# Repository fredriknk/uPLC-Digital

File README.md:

# μPLC-Digital
### Pcbway Sponsorship
Thanks so much to [PCBWay](https://www.pcbway.com/) who offered to assemble my first prototype batch of all three [uPLC modules](https://github.com/fredriknk/uPLC-stack). They deliver awesome quality as always, see the result for yourself below.

 I now have two prototypes of the uPLC-Digital so ESP-Home integrations will come soon.

ESP micro PLC the size of a post stamp. 

The uPLC-digital version is an [ESP-32-C3](./DOCUMENTATION/esp-12f_product_specification_en.pdf) wifi, bluetooth module for communication and MCU, it has a 3.8-24V buck regulator, has three 2.5-25V inputs, three 2.5-25v 100ma high speed open drain outputs through a [TBD062003](./DOCUMENTATION/Transistor-array-2304140030_TOSHIBA-TBD62003AFWG_C114084.pdf) DMOS transistor array ic. And one protected 3.3v GPIO for onwire communication (Eg for DS18b20 sensors). The digital version allso has input voltage monitoring for battery applications. 

The HO HI ports can be configured to be inputs or outputs by jumping solder bridges one each side of the IC. By default 1-3 are outputs and 4-6 are inputs. 

[Schematic](./DOCUMENTATION/_schematic.pdf)

[Assembly IBOM](https://htmlpreview.github.io/?https://raw.githubusercontent.com/fredriknk/uplc-digital/main/DOCUMENTATION/ibom.html)

## Specifications
| **Parameter**   | **Description**                                                     |
|-----------------|---------------------------------------------------------------------|
| _Input voltage_ | 3.8-24v                               |
| _Current_       | TBD Wifi: ##mA, Radio Off: ##mA, Deep sleep ##uA |  
| _Communication_ | 2.4ghz WIFI, Uart TTL                            |
| _Baudrate_      | 115200                                                              |
| _PCB size_      | 21x31.4mm                                                             |
| _PCB info_      | 1.6mm FR4, HASL lead free, 4 layer               |
| _Case size_     | XxXxXmm TBD                                                         |

## FIRST PRODUCTION PROTOTYPE
TODO

## Connector

| **Label**   | **GPIO**|**Description**       |
|------------|-----|-------------------------|
|_3V3_ | 3V3 | 3.3v output for sensor connection |
|_ONE-W_ | GPIO18  | Protected gpio for onewire comm |
|_GND_ | GND | GND port for sensor connection|
|_GND_ | GND | GND port for sensor connection |
|_HO-06_ | GPIO10  | 25v 100ma open drain output |
|_HO-05_ | GPIO19  | 25v 100ma open drain output |
|_HO-04_ | GPIO3  | 25v 100ma open drain output |
|_HI-03_ | GPIO7  | 2.5-25v input (with pulldown) |
|_HI-02_ | GPIO6  | 2.5-25v input (with pulldown) |
|_HI-01_ | GPIO5  | 2.5-25v input (with pulldown) |
|_GND_ | GND |  Ground  |
|_4-24V_ | Buck reg |3.8-24v polarity protected input |

## PCB Pictures
PCB assembly by [PCBWay](https://www.pcbway.com/)

## Homeassistant Implementation
TODO

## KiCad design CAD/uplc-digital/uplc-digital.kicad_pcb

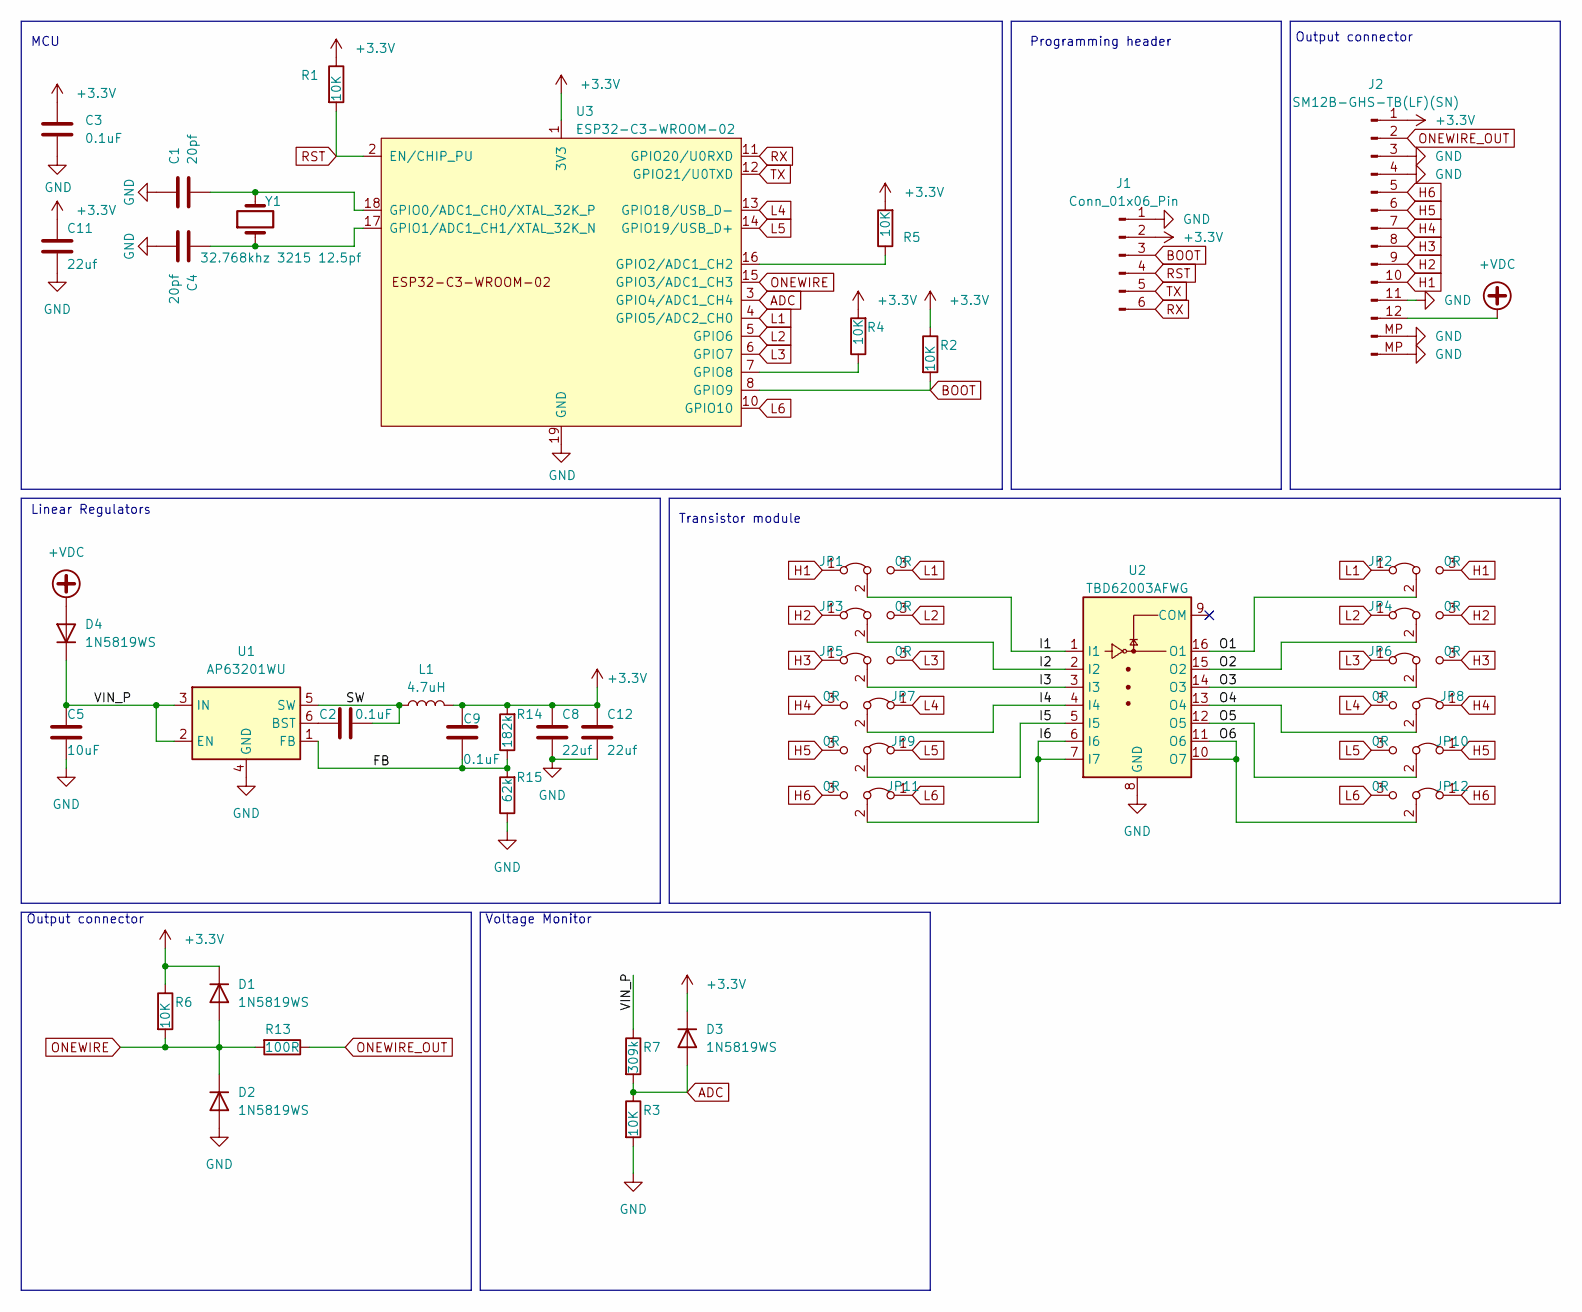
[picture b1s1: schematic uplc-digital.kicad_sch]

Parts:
C1, C4: 20pf; C_0402_1005Metric; MPN 0402CG200J500NT; LCSC Part # C1554
C2, C3, C9: 0.1uF; C_0402_1005Metric; MPN GRM155R71H104KE14D; LCSC Part # C77020
C5: 10uF; C_0805_2012Metric; MPN GRM21BR6YA106KE43L; LCSC Part # C162422
C8, C11, C12: 22uf; C_0402_1005Metric; MPN GRM155R60J226ME11D; LCSC Part # C415703
D1, D2, D3, D4: 1N5819WS; D_SOD-323; MPN 1N5819WS; LCSC Part # C191023
J1: Conn_01x06_Pin; TestPoint_Pad_1.0x1.0mm_6pad; LCSC Part # DNP
J2: SM12B-GHS-TB(LF)(SN); JST_GH_SM12B-GHS-TB_1x12-1MP_P1.25mm_Horizontal; MPN SM12B-GHS-TB(LF)(SN); LCSC Part # C265421
JP1, JP2, JP3, JP4, JP5, JP6, JP7, JP8, JP9, JP10, JP11, JP12: 0R; SolderJumper-3_P1.3mm_BridgedSMD12_0402; MPN RTT02000JTH; LCSC Part # C102746
L1: 4.7uH; L_1008_2520Metric; MPN LQM2HPN4R7MG0L; LCSC Part # C82314
R1, R2, R3, R4, R5, R6: 10K; R_0402_1005Metric; MPN 0402WGF1002TCE; LCSC Part # C25744
R7: 309k; R_0402_1005Metric; MPN RTT023093FTH; LCSC Part # C159040
R13: 100R; R_0402_1005Metric; MPN 0402WGF1000TCE; LCSC Part # C25076
R14: 182k; R_0402_1005Metric; MPN 0402WGF1823TCE; LCSC Part # C11481
R15: 62k; R_0402_1005Metric; MPN RC0402FR-0762KL; LCSC Part # C137950
U1: AP63201WU; TSOT-23-6; MPN AP63201WU-7; LCSC Part # C2071044
U2: TBD62003AFWG; SOIC-16_3.9x9.9mm_P1.27mm; MPN TBD62003AFWG; LCSC Part # C114084
U3: ESP32-C3-WROOM-02; MPN ESP32-C3-WROOM-02-N4; LCSC Part # C2934560
Y1: 32.768khz 3215 12.5pf; Crystal_SMD_3215-2Pin_3.2x1.5mm; MPN Q13FC13500004; LCSC Part # C32346

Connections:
+3.3V: C3.1, C8.1, C9.1, C11.1, C12.1, D1.1 (K), D3.1 (K), J1.2, J2.1, L1.2, R1.1, R2.1, R4.2, R5.2, R6.1, R14.2, U3.1 (3V3)
+VDC: D4.2 (A), J2.12
/FB: C9.2, R14.1, R15.2, U1.1 (FB)
/I1: JP1.2 (C), U2.1 (I1)
/I2: JP3.2 (C), U2.2 (I2)
/I3: JP5.2 (C), U2.3 (I3)
/I4: JP7.2 (C), U2.4 (I4)
/I5: JP9.2 (C), U2.5 (I5)
/I6: JP11.2 (C), U2.6 (I6), U2.7 (I7)
/O1: JP2.2 (C), U2.16 (O1)
/O2: JP4.2 (C), U2.15 (O2)
/O3: JP6.2 (C), U2.14 (O3)
/O4: JP8.2 (C), U2.13 (O4)
/O5: JP10.2 (C), U2.12 (O5)
/O6: JP12.2 (C), U2.10 (O7), U2.11 (O6)
/SW: C2.1, L1.1, U1.5 (SW)
/VIN_P: C5.1, D4.1 (K), R7.1, U1.2 (EN), U1.3 (IN)
ADC: D3.2 (A), R3.1, R7.2, U3.3 (GPIO4/ADC1_CH4)
BOOT: J1.3, R2.2, U3.8 (GPIO9)
GND: C1.1, C3.2, C4.2, C5.2, C8.2, C11.2, C12.2, D2.2 (A), J1.1, J2.3, J2.4, J2.11, J2.MP (Pin_13), R3.2, R15.1, U1.4 (GND), U2.8 (GND), U3.9 (GND), U3.19 (GND)
H1: J2.10, JP1.1 (A), JP2.3 (B)
H2: J2.9, JP3.1 (A), JP4.3 (B)
H3: J2.8, JP5.1 (A), JP6.3 (B)
H4: J2.7, JP7.3 (B), JP8.1 (A)
H5: J2.6, JP9.3 (B), JP10.1 (A)
H6: J2.5, JP11.3 (B), JP12.1 (A)
L1: JP1.3 (B), JP2.1 (A), U3.4 (GPIO5/ADC2_CH0)
L2: JP3.3 (B), JP4.1 (A), U3.5 (GPIO6)
L3: JP5.3 (B), JP6.1 (A), U3.6 (GPIO7)
L4: JP7.1 (A), JP8.3 (B), U3.13 (GPIO18/USB_D-)
L5: JP9.1 (A), JP10.3 (B), U3.14 (GPIO19/USB_D+)
L6: JP11.1 (A), JP12.3 (B), U3.10 (GPIO10)
unnamed: C2.2, U1.6 (BST)
unnamed: C1.2, U3.18 (GPIO0/ADC1_CH0/XTAL_32K_P), Y1.2
unnamed: C4.1, U3.17 (GPIO1/ADC1_CH1/XTAL_32K_N), Y1.1
unnamed: R5.1, U3.16 (GPIO2/ADC1_CH2)
unnamed: R4.1, U3.7 (GPIO8)
ONEWIRE: D1.2 (A), D2.1 (K), R6.2, R13.2, U3.15 (GPIO3/ADC1_CH3)
ONEWIRE_OUT: J2.2, R13.1
RST: J1.4, R1.2, U3.2 (EN/CHIP_PU)
RX: J1.6, U3.11 (GPIO20/U0RXD)
TX: J1.5, U3.12 (GPIO21/U0TXD)

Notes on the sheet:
Transistor module
Linear Regulators
MCU
Output connector
Programming header
Voltage Monitor

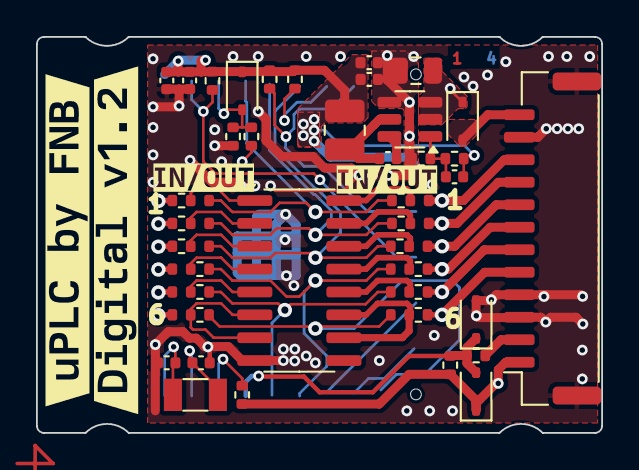
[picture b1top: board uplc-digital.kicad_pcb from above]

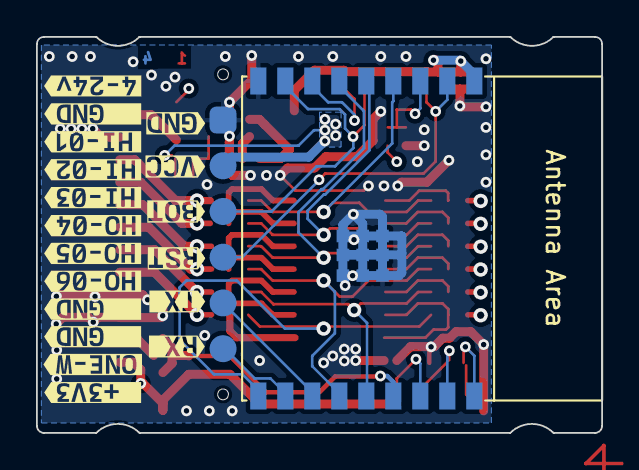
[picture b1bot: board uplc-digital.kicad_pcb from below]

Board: 4 copper layers, 31.4 x 22.0 mm, 64 parts (20 on the bottom side), 42 nets.

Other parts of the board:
kibuzzard-65D8B0E2: G***; kibuzzard-65D8B0E2
kibuzzard-65D8B0ED: G***; kibuzzard-65D8B0ED
kibuzzard-65D8B0F8: G***; kibuzzard-65D8B0F8
kibuzzard-65D8B10C: G***; kibuzzard-65D8B10C
kibuzzard-65D8B28C: G***; kibuzzard-65D8B28C
kibuzzard-65D8B104: G***; kibuzzard-65D8B104
kibuzzard-65D8B121: G***; kibuzzard-65D8B121
kibuzzard-65D8B297: G***; kibuzzard-65D8B297
kibuzzard-65D8B343: G***; kibuzzard-65D8B343
kibuzzard-65D74DE1: G***; kibuzzard-65D74DE1
kibuzzard-65D74DEE: G***; kibuzzard-65D74DEE
kibuzzard-65D74DFB: G***; kibuzzard-65D74DFB
kibuzzard-65D460A0: G***; kibuzzard-65D460A0
kibuzzard-65D3616E: G***; kibuzzard-65D3616E
kibuzzard-65D7176D: G***; kibuzzard-65D7176D
kibuzzard-65D7177B: G***; kibuzzard-65D7177B
kibuzzard-65D36177: G***; kibuzzard-65D36177
kibuzzard-65D46022: G***; kibuzzard-65D46022
kibuzzard-65D46066: G***; kibuzzard-65D46066
kibuzzard-65D49092: G***; kibuzzard-65D49092
kibuzzard-65D71774: G***; kibuzzard-65D71774
kibuzzard-65DCA831: G***; kibuzzard-65DCA831

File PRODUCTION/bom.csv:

Designator,Footprint,Quantity,Value,LCSC Part #
"C1, C4",0402,2,20pf,C1554
"C11, C12, C8",0402,3,22uf,C415703
"C2, C3, C9",0402,3,0.1uF,C307331
C5,0805,1,10uF,C162422
"D1, D2, D3, D4",D_SOD-323,4,1N5819WS,C191023
J1,TestPoint_Pad_1.0x1.0mm_6pad,1,Conn_01x06_Pin,DNP
J2,JST_GH_SM12B-GHS-TB_1x12-1MP_P1.25mm_Horizontal,1,SM12B-GHS-TB(LF)(SN),C265421
"JP1, JP10, JP11, JP12, JP2, JP3, JP4, JP5, JP6, JP7, JP8, JP9",SolderJumper-3_P1.3mm_BridgedSMD12_0402,12,0R,
L1,1008,1,6.8uH,C98340
"R1, R2, R3, R4, R5, R6",0402,6,10K,C25744
R13,0402,1,100R,C25076
R14,0402,1,182k,C11481
R15,0402,1,62k,C137950
R7,0402,1,309k,
U1,TSOT-23-6,1,AP63201WU,C2071044
U2,SOIC-16_3.9x9.9mm_P1.27mm,1,TBD62003AFWG,C114084
U3,ESP32-C3-WROOM-02,1,ESP32-C3-WROOM-02,C2934560
Y1,Crystal_SMD_3215-2Pin_3.2x1.5mm,1,32.768khz 3215 12.5pf,C32346

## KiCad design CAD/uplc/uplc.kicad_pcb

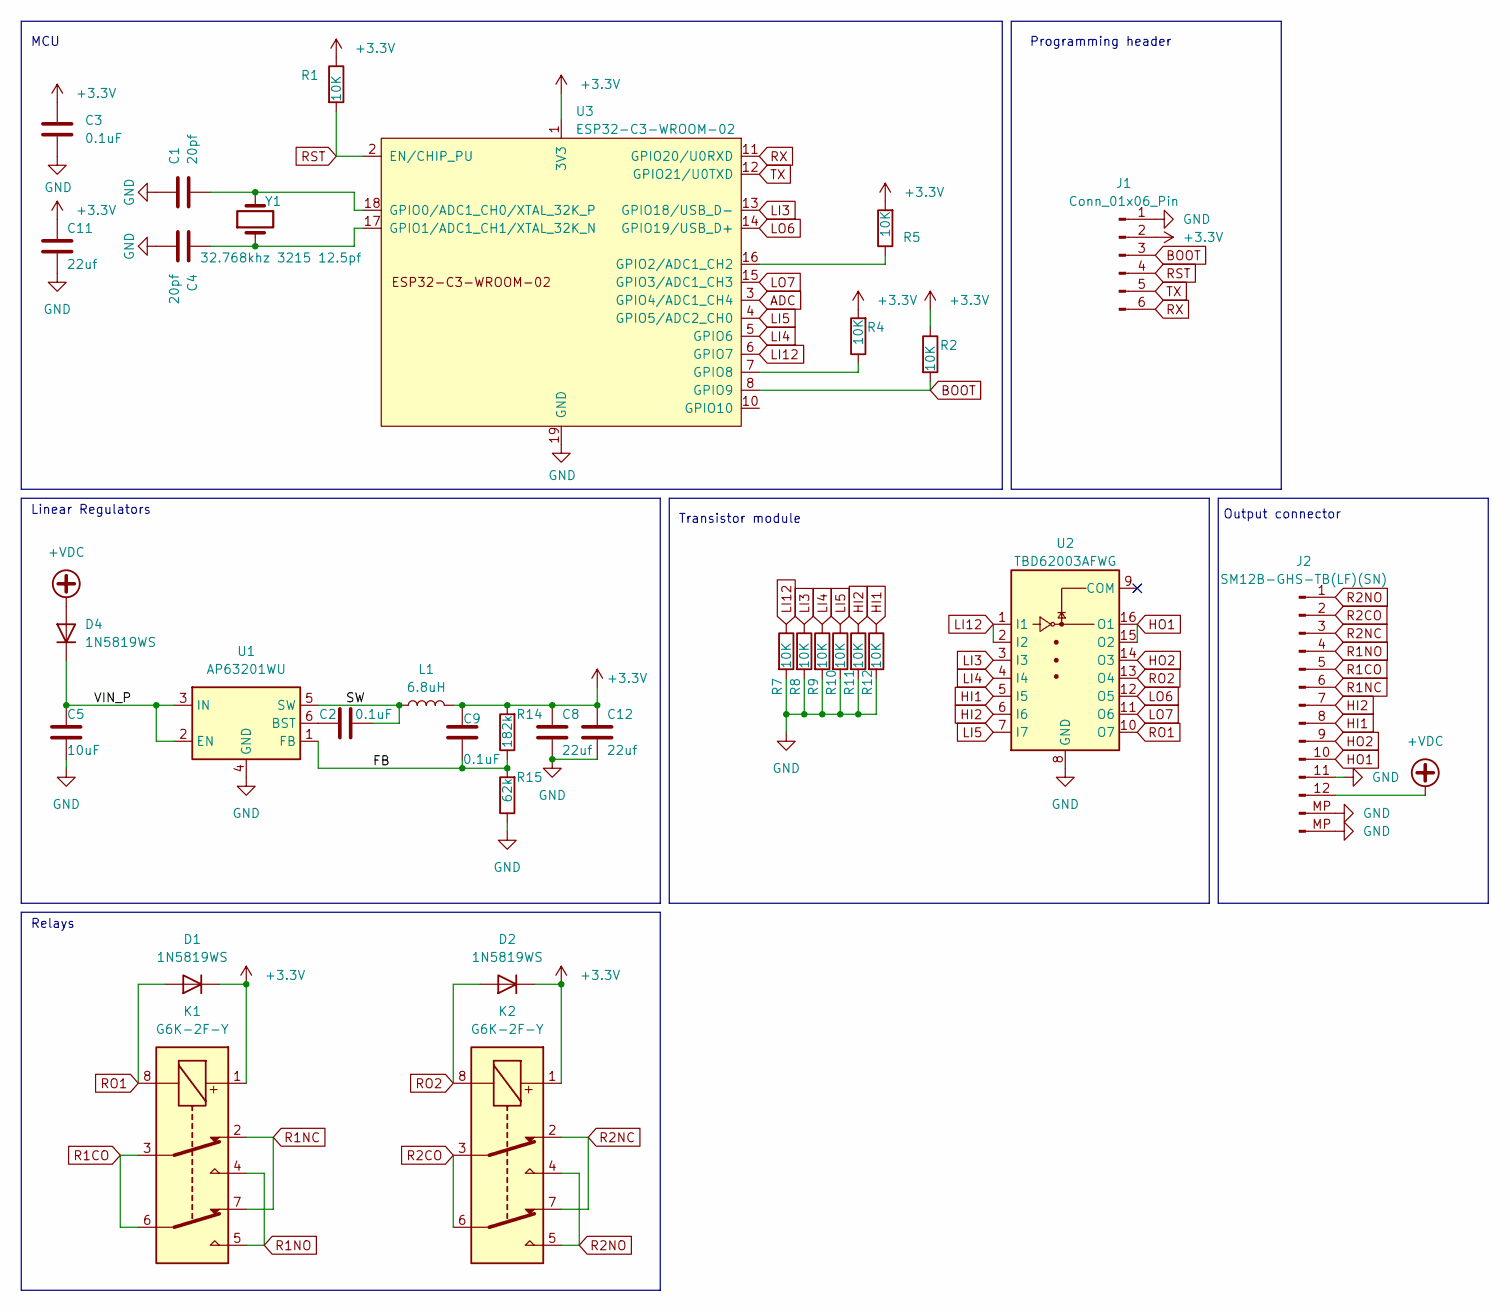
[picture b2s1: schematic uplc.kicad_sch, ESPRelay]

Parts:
C1, C4: 20pf; C_0402_1005Metric; LCSC Part # C1554
C2, C3, C9: 0.1uF; C_0402_1005Metric; LCSC Part # C307331
C5: 10uF; C_0805_2012Metric; LCSC Part # C162422
C8, C11, C12: 22uf; C_0402_1005Metric; LCSC Part # C415703
D1, D2, D4: 1N5819WS; D_SOD-323; LCSC Part # C191023
J1: Conn_01x06_Pin; TestPoint_Pad_1.0x1.0mm_6pad; LCSC Part # DNP
J2: SM12B-GHS-TB(LF)(SN); JST_GH_SM12B-GHS-TB_1x12-1MP_P1.25mm_Horizontal; LCSC Part # C265421
K1, K2: G6K-2F-Y; Relay_DPDT_Omron_G6K-2F-Y; LCSC Part # C2982926
L1: 6.8uH; L_1008_2520Metric; LCSC Part # C98340
R1, R2, R4, R5, R7, R8, R9, R10, R11, R12: 10K; R_0402_1005Metric; LCSC Part # C25744
R14: 182k; R_0402_1005Metric; LCSC Part # C11481
R15: 62k; R_0402_1005Metric; LCSC Part # C137950
U1: AP63201WU; TSOT-23-6; LCSC Part # C2071044
U2: TBD62003AFWG; SOIC-16_3.9x9.9mm_P1.27mm; LCSC Part # C114084
U3: ESP32-C3-WROOM-02; LCSC Part # C2934560
Y1: 32.768khz 3215 12.5pf; Crystal_SMD_3215-2Pin_3.2x1.5mm; LCSC Part # C32346

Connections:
+3.3V: C3.1, C8.1, C9.1, C11.1, C12.1, D1.1 (K), D2.1 (K), J1.2, K1.1, K2.1, L1.2, R1.1, R2.1, R4.2, R5.2, R14.2, U3.1 (3V3)
+VDC: D4.2 (A), J2.12
/FB: C9.2, R14.1, R15.2, U1.1 (FB)
/SW: C2.1, L1.1, U1.5 (SW)
/VIN_P: C5.1, D4.1 (K), U1.2 (EN), U1.3 (IN)
ADC: U3.3 (GPIO4/ADC1_CH4)
BOOT: J1.3, R2.2, U3.8 (GPIO9)
GND: C1.1, C3.2, C4.2, C5.2, C8.2, C11.2, C12.2, J1.1, J2.11, J2.MP (Pin_14), R7.2, R8.2, R9.2, R10.2, R11.2, R12.2, R15.1, U1.4 (GND), U2.8 (GND), U3.9 (GND), U3.19 (GND)
HI1: J2.8, R12.1, U2.5 (I5)
HI2: J2.7, R11.1, U2.6 (I6)
HO1: J2.10, U2.15 (O2), U2.16 (O1)
HO2: J2.9, U2.14 (O3)
LI3: R8.1, U2.3 (I3), U3.13 (GPIO18/USB_D-)
LI4: R9.1, U2.4 (I4), U3.5 (GPIO6)
LI5: R10.1, U2.7 (I7), U3.4 (GPIO5/ADC2_CH0)
LI12: R7.1, U2.1 (I1), U2.2 (I2), U3.6 (GPIO7)
LO6: U2.12 (O5), U3.14 (GPIO19/USB_D+)
LO7: U2.11 (O6), U3.15 (GPIO3/ADC1_CH3)
unnamed: C2.2, U1.6 (BST)
unnamed: C1.2, U3.18 (GPIO0/ADC1_CH0/XTAL_32K_P), Y1.2
unnamed: C4.1, U3.17 (GPIO1/ADC1_CH1/XTAL_32K_N), Y1.1
unnamed: R5.1, U3.16 (GPIO2/ADC1_CH2)
unnamed: R4.1, U3.7 (GPIO8)
R1CO: J2.5, K1.3, K1.6
R1NC: J2.6, K1.2, K1.7
R1NO: J2.4, K1.4, K1.5
R2CO: J2.2, K2.3, K2.6
R2NC: J2.3, K2.2, K2.7
R2NO: J2.1, K2.4, K2.5
RO1: D1.2 (A), K1.8, U2.10 (O7)
RO2: D2.2 (A), K2.8, U2.13 (O4)
RST: J1.4, R1.2, U3.2 (EN/CHIP_PU)
RX: J1.6, U3.11 (GPIO20/U0RXD)
TX: J1.5, U3.12 (GPIO21/U0TXD)

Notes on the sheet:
Transistor module
Linear Regulators
MCU
Output connector
Programming header
Relays

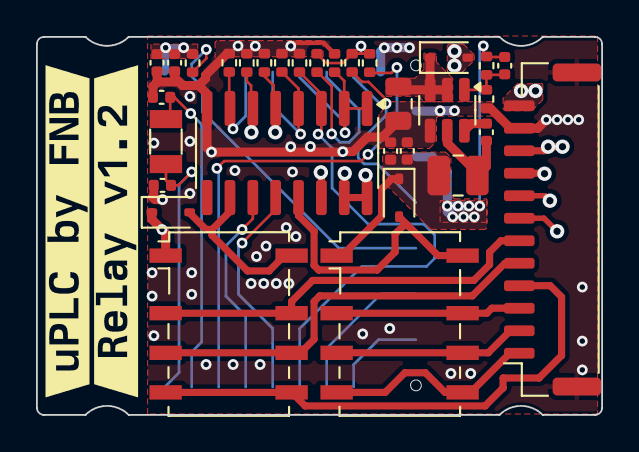
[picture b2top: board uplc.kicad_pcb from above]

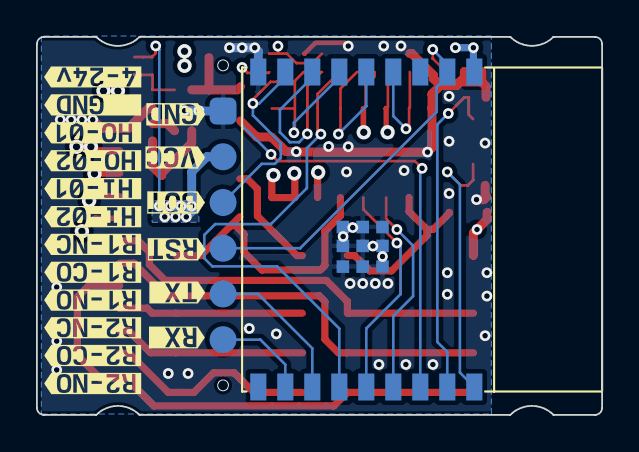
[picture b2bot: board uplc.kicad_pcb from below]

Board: 4 copper layers, 31.4 x 21.0 mm, 53 parts (20 on the bottom side), 33 nets.

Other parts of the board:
kibuzzard-65D6FF37: G***; kibuzzard-65D6FF37
kibuzzard-65D361A7: G***; kibuzzard-65D361A7
kibuzzard-65D361B0: G***; kibuzzard-65D361B0
kibuzzard-65D361D3: G***; kibuzzard-65D361D3
kibuzzard-65D361E1: G***; kibuzzard-65D361E1
kibuzzard-65D361E9: G***; kibuzzard-65D361E9
kibuzzard-65D361F2: G***; kibuzzard-65D361F2
kibuzzard-65D361FD: G***; kibuzzard-65D361FD
kibuzzard-65D460A0: G***; kibuzzard-65D460A0
kibuzzard-65D3616E: G***; kibuzzard-65D3616E
kibuzzard-65D3619D: G***; kibuzzard-65D3619D
kibuzzard-65D3620E: G***; kibuzzard-65D3620E
kibuzzard-65D7176D: G***; kibuzzard-65D7176D
kibuzzard-65D7177B: G***; kibuzzard-65D7177B
kibuzzard-65D36177: G***; kibuzzard-65D36177
kibuzzard-65D36206: G***; kibuzzard-65D36206
kibuzzard-65D46022: G***; kibuzzard-65D46022
kibuzzard-65D46066: G***; kibuzzard-65D46066
kibuzzard-65D49092: G***; kibuzzard-65D49092
kibuzzard-65D71774: G***; kibuzzard-65D71774

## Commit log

2024-02-22 Fork uplc
2024-02-22 Rev 1.0
2024-02-23 WIP rev 1.1
2024-02-23 Rev 1.1 Schem PCB done
2024-02-26 Rev 1.1 Push for production
2024-02-26 Rev 1.2
2024-10-14 Panelization changes
2025-04-09 Feat: Picture update
2025-04-09 Feat: V1.1
